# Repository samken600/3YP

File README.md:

# 3YP

## [Project Workspace](project_workspace)

See the [README](project_workspace/README.md) inside for details on setting up RIOT. Note that the RIOT and openocd sub-repositories are managed with git subtrees, NOT submodules. Ensure the correct commands are used when updating these modules.

* Border router files to run on SAMR30 Xplained-Pro boards (`/gnrc_border_router`)

* CoAP server to run on PCBs (`/3yp_node_coap`)

* Testing program to run on PCBs (`/3yp_node_testing`)

* NanoCoAP server to run on SAMR21 boards with DS18 temperature sensor (`/nanocoap_server`)

* Modified RIOT directory (`/RIOT`)

* CoAP server using SAUL, designed to work with different hardware, providing access to LEDs, a temperature sensor and TX power (`/3yp_node_coap_saul`)

* CoAP server and client for automatically PUTting sensor readings and self timestamping packets, designed to work with [coap\_server](coap_server/) and [coap\_forwarder](coap_forwarder) (`3yp_node_coap_saul_puts`)

* Power management testing programs, with and without networking (`periph_pm`, `periph_pm_networking`)

## [PCB Files](pcb/)

* Parts list for PCB
* [Eagle project files](pcb/EAGLE/) (see `/projects/3YP PCB Rev2A` for project and `/libraries` for parts). Can use this as the working directory for EAGLE. 

## [CoAP to HTTP query script](coap-http/)

* Bridge between CoAP and HTTP

* Scheduled script runs every 10 minutes (`coap-http/pipe.py`)

## [Flask Application](flaskApp/)

* Flask webserver files
* HTML and CSS (`/app/static`)
* Temperature HTTP API (`/app/controllers`)
* Graphing webpage/dashboard (`/plotlydash`)

## [Coap Forwarder](coap_forwarder/)

* Using CoAPthon3 with binary token patch
* Acts as forwarder between IPv6 GNRC network and IPv4 outer network
* Only role is to forward packets outside of network

## [Coap Server](coap_server/)

* Using CoAPthon3 with binary token patch
* Provides API to POST temperature data to and GET the current time
* Interfaced with MongoDB in `config.py` and so data served via the flask webserver

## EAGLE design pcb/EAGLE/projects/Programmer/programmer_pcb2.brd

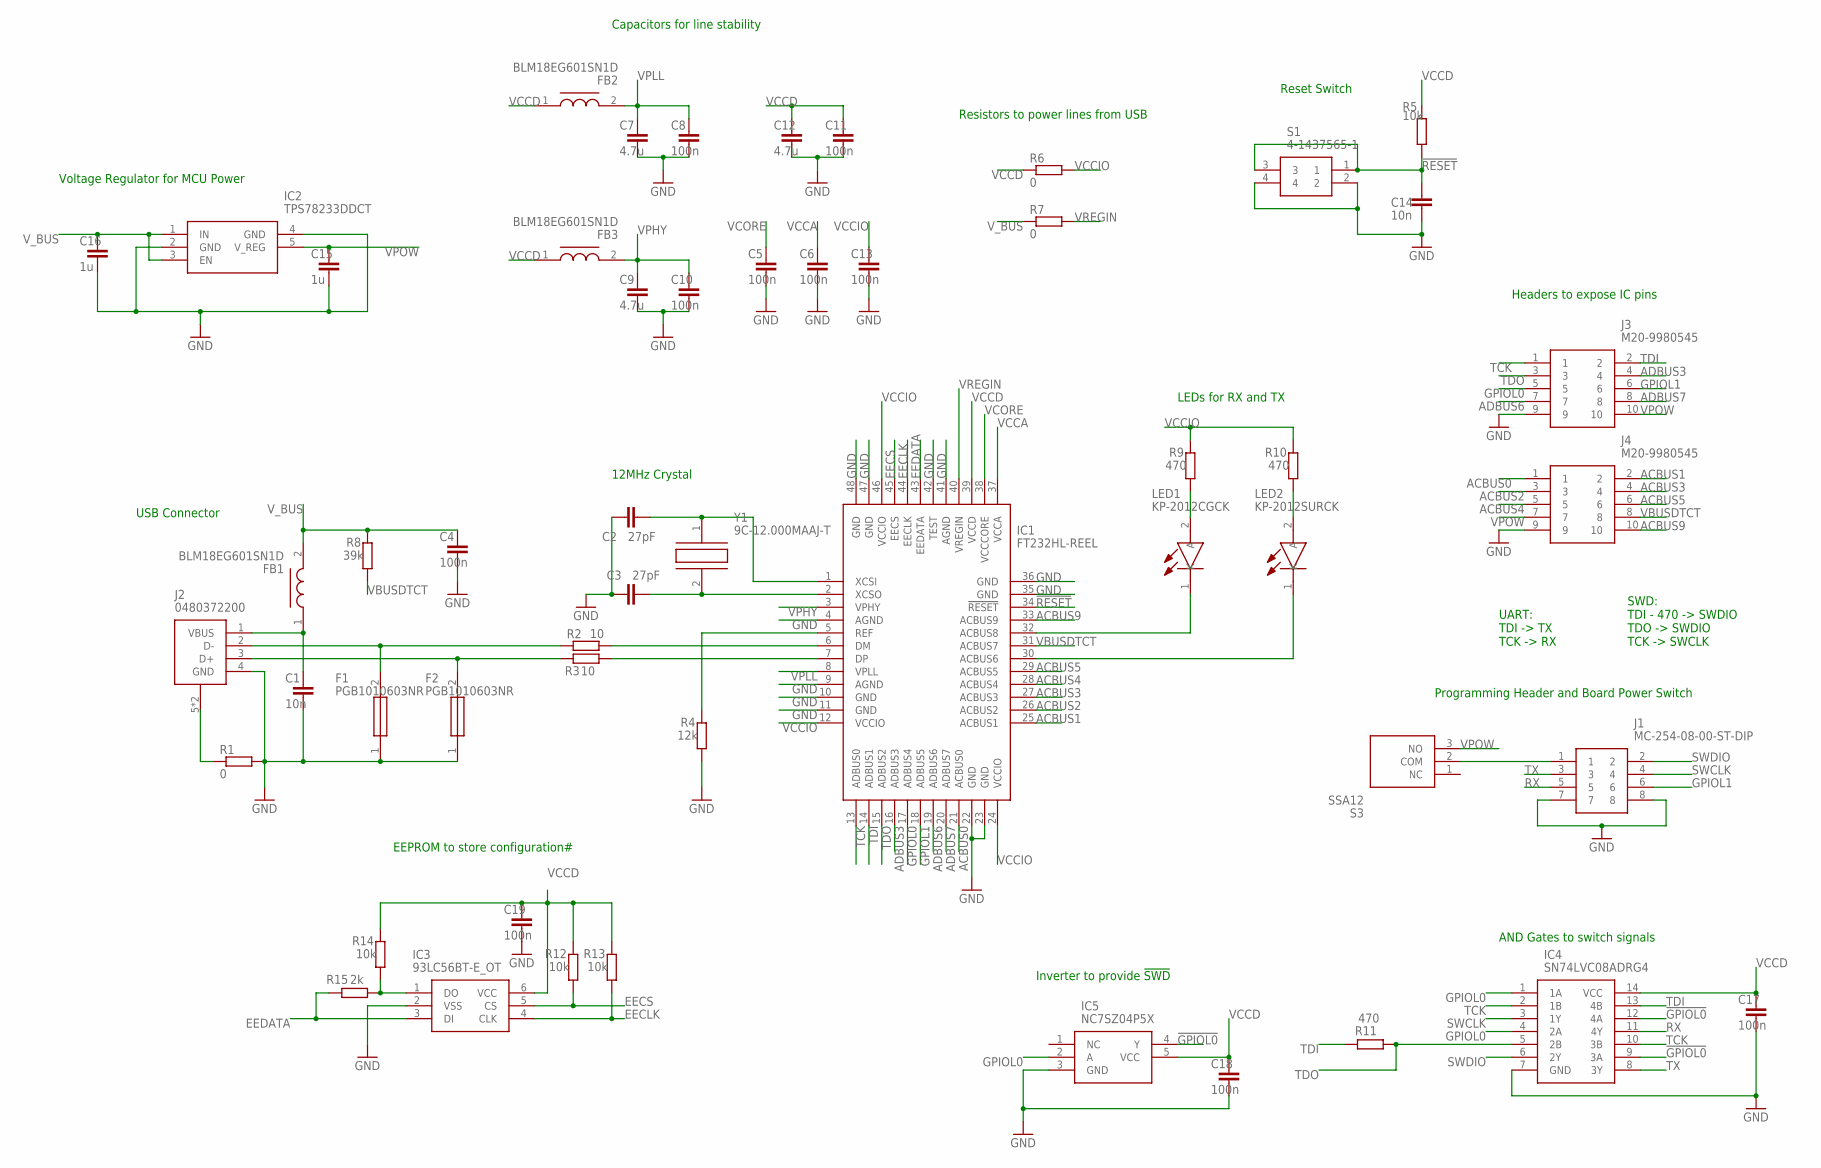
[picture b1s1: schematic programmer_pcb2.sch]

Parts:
C1, C14: 10n; C0805
C2, C3: 27pF; C0805
C4, C5, C6, C8, C10, C11, C13, C17, C18, C19: 100n; C0805
C7, C9, C12: 4.7u; C0805
C15, C16: 1u; C0805
F1, F2: PGB1010603NR; FUSC1708X36N
FB1, FB2, FB3: BLM18EG601SN1D; BLM18EG121SH1D
IC1: FT232HL-REEL; QFP50P900X900X160-48N
IC2: TPS78233DDCT; SOT95P280X110-5N
IC3: 93LC56BT-E_OT; SOT95P270X145-6N
IC4: SN74LVC08ADRG4; SOIC127P600X175-14N
IC5: NC7SZ04P5X; SOT65P210X110-5N
J1: MC-254-08-00-ST-DIP; MC2540800STDIP
J2: 0480372200
J3, J4: M20-9980545; HDRV10W80P254_2X5_1270X508X864
LED1: KP-2012CGCK; LEDC2012X110N
LED2: KP-2012SURCK; LEDC2012X110N
R1, R6, R7: 0; R0603
R2, R3: 10; R0603
R4: 12k; R0603
R5, R12, R13, R14: 10k; R0603
R8: 39k; R0603
R9, R10, R11: 470; R0603
R15: 2k; R0603
S1: 4-1437565-1; FSM-SWITCH
S3: SSA12
Y1: 9C-12.000MAAJ-T; SMD-HC-49-S

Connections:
!GPIOL0: IC4.9 (3A), IC4.12 (4A), IC5.4 (Y)
!RESET: C14.1, IC1.34 (!RESET), R5.1, S1.1, S1.3
ACBUS0: IC1.21 (ACBUS0), J4.1
ACBUS1: IC1.25 (ACBUS1), J4.2
ACBUS2: IC1.26 (ACBUS2), J4.3
ACBUS3: IC1.27 (ACBUS3), J4.4
ACBUS4: IC1.28 (ACBUS4), J4.5
ACBUS5: IC1.29 (ACBUS5), J4.6
ACBUS9: IC1.33 (ACBUS9), J4.10
ADBUS3: IC1.16 (ADBUS3), J3.4
ADBUS6: IC1.19 (ADBUS6), J3.7
ADBUS7: IC1.20 (ADBUS7), J3.8
EECLK: IC1.44 (EECLK), IC3.4 (CLK), R13.1
EECS: IC1.45 (EECS), IC3.5 (CS), R12.1
EEDATA: IC1.43 (EEDATA), IC3.3 (DI), R15.1
GND: C1.2, C2.1, C3.1, C4.2, C5.2, C6.2, C7.2, C8.2, C9.2, C10.2, C11.2, C12.2, C13.2, C14.2, C15.2, C16.2, C17.2, C18.2, C19.2, F1.1, F2.1, IC1.4 (AGND), IC1.9 (AGND), IC1.10 (GND), IC1.11 (GND), IC1.22 (GND), IC1.23 (GND), IC1.35 (GND), IC1.36 (GND), IC1.41 (AGND), IC1.42 (TEST), IC1.47 (GND), IC1.48 (GND), IC2.2 (GND), IC2.4 (GND), IC3.2 (VSS), IC4.7 (GND), IC5.3 (GND), J1.7, J1.8, J2.4 (GND), J3.9, J4.9, R1.2, R4.1, S1.2, S1.4
GPIOL0: IC1.17 (ADBUS4), IC4.1 (1A), IC4.4 (2A), IC5.2 (A), J3.5
GPIOL1: IC1.18 (ADBUS5), J1.6, J3.6
unnamed: J2.5 (SLD), J2.6 (SLD), R1.1
unnamed: C1.1, FB1.1, J2.1 (VBUS)
unnamed: F1.2, J2.2 (D-), R2.1
unnamed: F2.2, J2.3 (D+), R3.1
unnamed: IC1.7 (DP), R3.2
unnamed: IC1.6 (DM), R2.2
unnamed: C2.2, IC1.1 (XCSI), Y1.1
unnamed: C3.2, IC1.2 (XCSO), Y1.2
unnamed: IC1.5 (REF), R4.2
unnamed: J1.1, S3.2 (COM)
unnamed: IC1.30 (ACBUS6), LED2.1 (K)
unnamed: IC1.32 (ACBUS8), LED1.1 (K)
unnamed: LED1.2 (A), R9.1
unnamed: LED2.2 (A), R10.1
unnamed: IC3.1 (DO), R14.1, R15.2
RX: IC4.11 (4Y), J1.5
SWCLK: IC4.3 (1Y), J1.4
SWDIO: IC4.6 (2Y), J1.2
TCK: IC1.13 (ADBUS0), IC4.2 (1B), IC4.10 (3B), J3.1
TDI: IC1.14 (ADBUS1), IC4.13 (4B), J3.2, R11.1
TDO: IC1.15 (ADBUS2), IC4.5 (2B), J3.3, R11.2
TX: IC4.8 (3Y), J1.3
VBUSDTCT: IC1.31 (ACBUS7), J4.8, R8.1
VCCA: C6.1, IC1.37 (VCCA)
VCCD: C11.1, C12.1, C17.1, C18.1, C19.1, FB2.1, FB3.1, IC1.39 (VCCD), IC3.6 (VCC), IC4.14 (VCC), IC5.5 (VCC), R5.2, R6.1, R12.2, R13.2, R14.2
VCCIO: C13.1, IC1.12 (VCCIO), IC1.24 (VCCIO), IC1.46 (VCCIO), R6.2, R9.2, R10.2
VCORE: C5.1, IC1.38 (VCCCORE)
VPHY: C9.1, C10.1, FB3.2, IC1.3 (VPHY)
VPLL: C7.1, C8.1, FB2.2, IC1.8 (VPLL)
VPOW: C15.1, IC2.5 (V_REG), J3.10, J4.7, S3.3 (NO)
VREGIN: IC1.40 (VREGIN), R7.2
V_BUS: C4.1, C16.1, FB1.2, IC2.1 (IN), IC2.3 (EN), R7.1, R8.2

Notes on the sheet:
UART: TDI -> TX TCK -> RX
SWD: TDI - 470 -> SWDIO TDO -> SWDIO TCK -> SWCLK
Voltage Regulator for MCU Power
Capacitors for line stability
Resistors to power lines from USB
Reset Switch
Headers to expose IC pins
LEDs for RX and TX
Programming Header and Board Power Switch
AND Gates to switch signals
Inverter to provide !SWD
EEPROM to store configuration#
USB Connector
12MHz Crystal

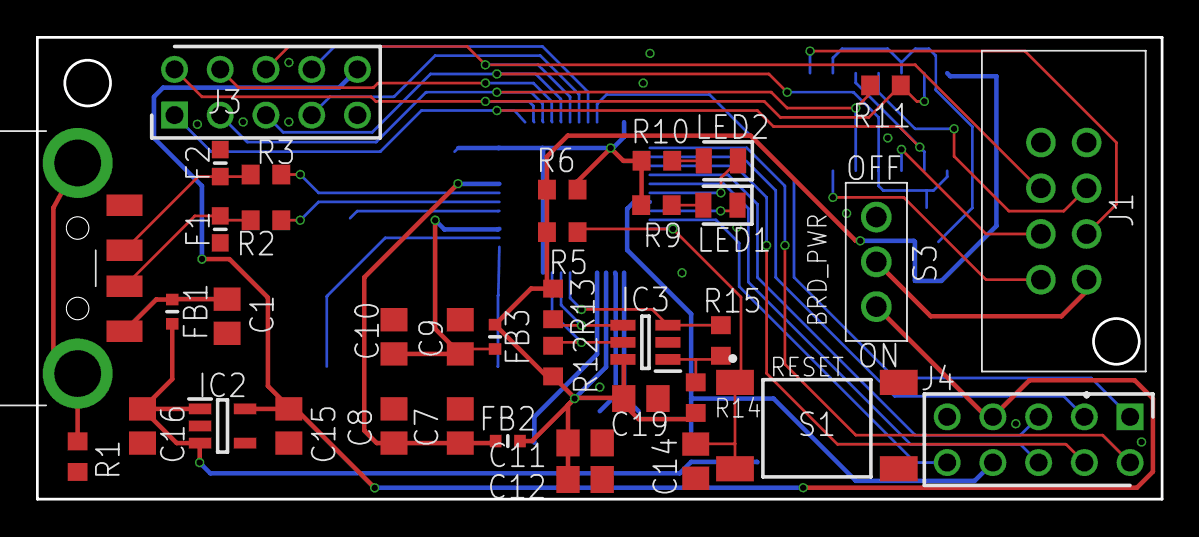
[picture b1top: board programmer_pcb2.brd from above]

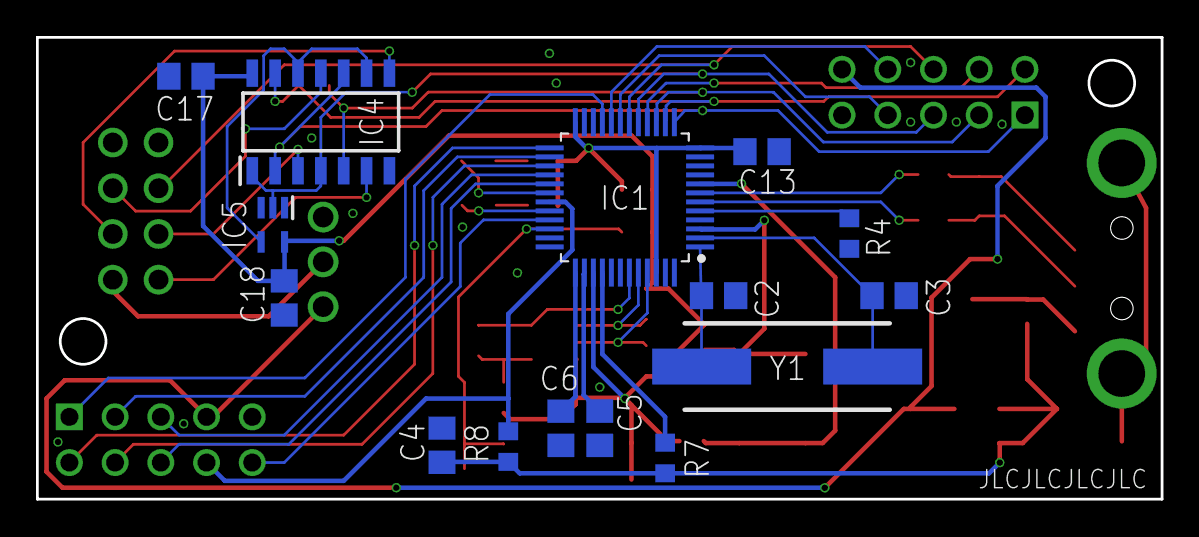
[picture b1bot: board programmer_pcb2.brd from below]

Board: 2 copper layers, 62.5 x 25.7 mm, 53 parts (15 on the bottom side), 50 nets.

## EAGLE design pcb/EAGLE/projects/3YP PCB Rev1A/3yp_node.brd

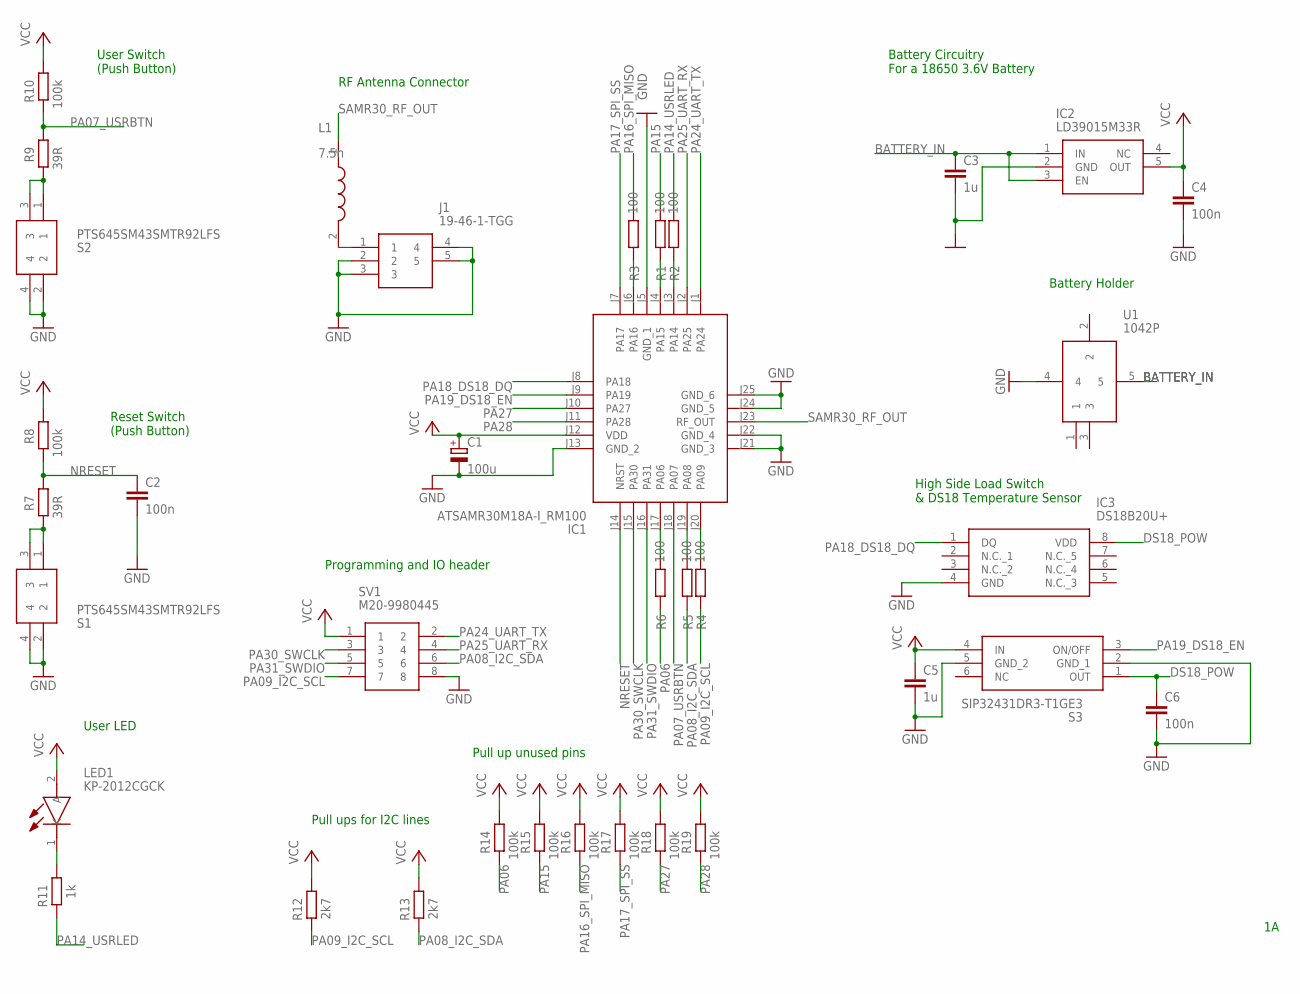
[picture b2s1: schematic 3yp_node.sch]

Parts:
C1: 100u; A/3216-18W
C2, C4, C6: 100n; C0805
C3, C5: 1u; C0805
IC1: ATSAMR30M18A-I_RM100; ATSAMR30M18AIRM100
IC2: LD39015M33R; SOT95P280X145-5N
IC3: DS18B20U+; SOP65P490X110-8N
J1: 19-46-1-TGG; 19-46-1-TGG_1
L1: 7.5n; INDC1006X60N
LED1: KP-2012CGCK; LEDC2012X110N
R1, R2, R3, R4, R5, R6: 100; R0603
R7, R9: 39R; R0603
R8, R10, R14, R15, R16, R17, R18, R19: 100k; R0603
R11: 1k; R0603
R12, R13: 2k7; R0603
S1, S2: PTS645SM43SMTR92LFS; PTS645(SMT)
S3: SIP32431DR3-T1GE3; SOT65P210X110-6N
SV1: M20-9980445; HDRV8W64P254_2X4_1016X508X868P
U1: 1042P

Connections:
BATTERY_IN: C3.1, IC2.1 (IN), IC2.3 (EN), U1.5
DS18_POW: C6.1, IC3.8 (VDD), S3.1 (OUT)
GND: C1.-, C2.2, C3.2, C4.2, C5.2, C6.2, IC1.J5 (GND_1), IC1.J13 (GND_2), IC1.J21 (GND_3), IC1.J22 (GND_4), IC1.J24 (GND_5), IC1.J25 (GND_6), IC2.2 (GND), IC3.4 (GND), J1.2, J1.3, J1.4, J1.5, S1.2, S1.4, S2.2, S2.4, S3.2 (GND_1), S3.5 (GND_2), SV1.8, U1.4
unnamed: R9.2, S2.1, S2.3
unnamed: IC1.J4 (PA15), R1.1
unnamed: IC1.J6 (PA16), R3.1
unnamed: IC1.J3 (PA14), R2.1
unnamed: IC1.J17 (PA06), R6.2
unnamed: IC1.J19 (PA08), R5.2
unnamed: IC1.J20 (PA09), R4.2
unnamed: R7.2, S1.1, S1.3
unnamed: LED1.1 (K), R11.1
unnamed: J1.1, L1.2
NRESET: C2.1, IC1.J14 (NRST), R7.1, R8.2
PA06: R6.1, R14.2
PA07_USRBTN: IC1.J18 (PA07), R9.1, R10.2
PA08_I2C_SDA: R5.1, R13.2, SV1.6
PA09_I2C_SCL: R4.1, R12.2, SV1.7
PA14_USRLED: R2.2, R11.2
PA15: R1.2, R15.2
PA16_SPI_MISO: R3.2, R16.2
PA17_SPI_SS: IC1.J7 (PA17), R17.2
PA18_DS18_DQ: IC1.J8 (PA18), IC3.1 (DQ)
PA19_DS18_EN: IC1.J9 (PA19), S3.3 (ON/OFF)
PA24_UART_TX: IC1.J1 (PA24), SV1.2
PA25_UART_RX: IC1.J2 (PA25), SV1.4
PA27: IC1.J10 (PA27), R18.2
PA28: IC1.J11 (PA28), R19.2
PA30_SWCLK: IC1.J15 (PA30), SV1.3
PA31_SWDIO: IC1.J16 (PA31), SV1.5
SAMR30_RF_OUT: IC1.J23 (RF_OUT), L1.1
VCC: C1.+, C4.1, C5.1, IC1.J12 (VDD), IC2.5 (OUT), LED1.2 (A), R8.1, R10.1, R12.1, R13.1, R14.1, R15.1, R16.1, R17.1, R18.1, R19.1, S3.4 (IN), SV1.1

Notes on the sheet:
Reset Switch (Push Button)
User Switch (Push Button)
Pull ups for I2C lines
High Side Load Switch & DS18 Temperature Sensor
Programming and IO header
Battery Circuitry For a 18650 3.6V Battery
User LED
RF Antenna Connector
Battery Holder
Pull up unused pins

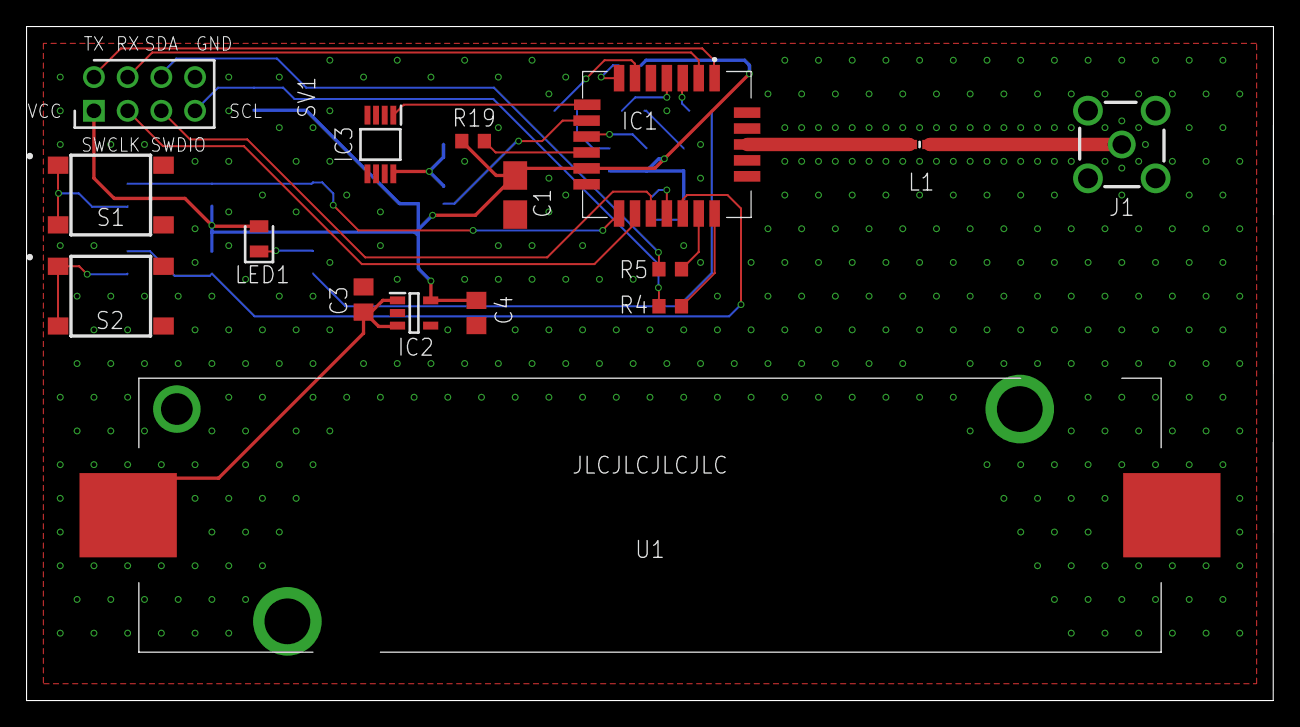
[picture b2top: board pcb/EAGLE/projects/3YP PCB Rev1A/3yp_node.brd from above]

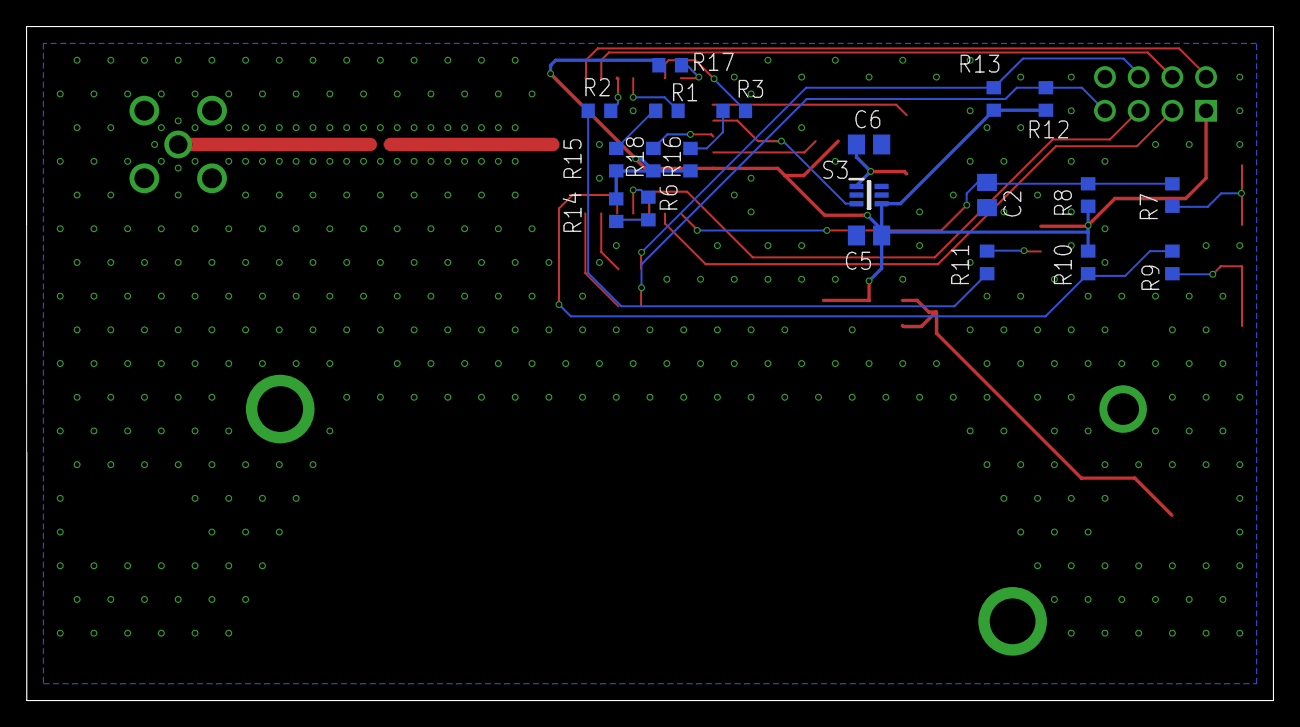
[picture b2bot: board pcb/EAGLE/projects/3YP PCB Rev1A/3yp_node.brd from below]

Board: 2 copper layers, 94.0 x 50.8 mm, 36 parts (20 on the bottom side), 32 nets.

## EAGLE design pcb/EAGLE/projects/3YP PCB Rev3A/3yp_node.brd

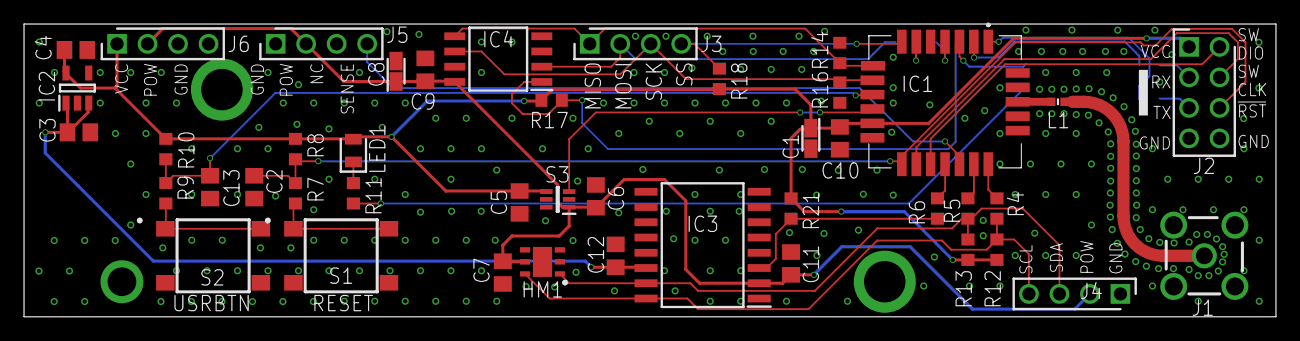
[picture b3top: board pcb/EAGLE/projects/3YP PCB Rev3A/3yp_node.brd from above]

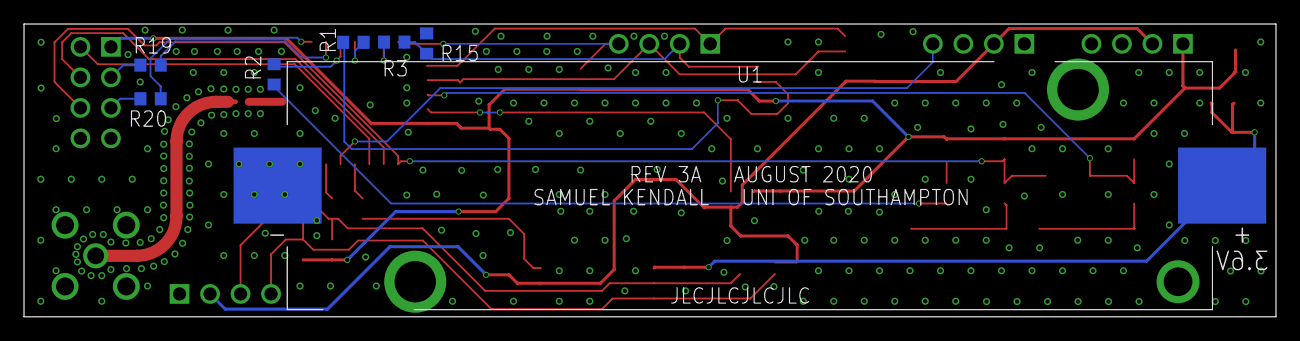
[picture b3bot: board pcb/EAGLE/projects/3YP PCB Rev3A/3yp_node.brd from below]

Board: 2 copper layers, 104.3 x 24.4 mm, 51 parts (7 on the bottom side), 34 nets.

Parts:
C1, C8: 10u; CAPPM2014X170N
C2, C6, C7, C9, C10, C11, C12, C13: 100n; C0805
C3, C4, C5: 1u; C0805
HM1: HDC1080DMBT; SON100P300X300X80-7N
IC1: ATSAMR30M18A-I_RM100; ATSAMR30M18AIRM100
IC2: TPS78233DDCT; SOT95P280X110-5N
IC3: DS3231SN#; SOIC127P1032X265-16N
IC4: AT25DF321A-SH-B; SOIC127P798X216-8N
J1: 19-46-1-TGG; 19-46-1-TGG_1
J2: M20-9980445; HDRV8W64P254_2X4_1016X508X868P
J3, J4, J5, J6: M20-9990445; HDRV4W64P0X254_1X4_1016X254X86
L1: 7.5n; INDC1006X60N
LED1: KP-2012CGCK; LEDC2012X110N
R1, R2, R3, R4, R5, R6: 100; R0603
R7, R9: 39R; R0603
R8, R10, R14, R15, R16, R17, R18, R21: 100k; R0603
R11, R19, R20: 1k; R0603
R12, R13: 2k7; R0603
S1, S2: PTS645SM43SMTR92LFS; PTS645(SMT)
S3: SIP32431DR3-T1GE3; SOT65P210X110-6N
U1: 1042P

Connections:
!PA15_SPI_FLASH_SS: IC4.1, R1.2, R17.2
BATTERY_IN: C3.1, C12.1, IC2.1, IC2.3, IC3.14, U1.5
GND: C1.2, C2.2, C3.2, C4.2, C5.2, C6.2, C7.2, C8.2, C9.2, C10.1, C11.2, C12.2, C13.2, HM1.2, HM1.3, HM1.4, IC1.J5, IC1.J13, IC1.J21, IC1.J22, IC1.J24, IC1.J25, IC2.2, IC2.4, IC3.5, IC3.6, IC3.7, IC3.8, IC3.9, IC3.10, IC3.11, IC3.12, IC3.13, IC4.4, J1.2, J1.3, J1.4, J1.5, J2.7, J2.8, J4.1, J5.1, J6.3, J6.4, R14.2, R15.2, R16.2, S1.3, S1.4, S2.3, S2.4, S3.2, S3.5, U1.4
unnamed: R9.2, S2.1, S2.2
unnamed: IC1.J4, R1.1
unnamed: IC1.J6, R3.1
unnamed: IC1.J3, R2.1
unnamed: IC1.J17, R6.2
unnamed: IC1.J19, R5.2
unnamed: IC1.J20, R4.2
unnamed: R7.2, S1.1, S1.2
unnamed: LED1.1, R11.1
unnamed: J1.1, L1.2
unnamed: IC1.J2, R19.1
unnamed: IC1.J1, R20.1
NRESET: C2.1, IC1.J14, J2.6, R7.1, R8.2
PA06_RTC_INT: IC3.3, R6.1, R21.2
PA07_ANALOG: IC1.J18, J5.4
PA08_I2C_SDA: HM1.1, IC3.15, J4.3, R5.1, R13.2
PA09_I2C_SCL: HM1.6, IC3.16, J4.4, R4.1, R12.2
PA14_USRLED: R2.2, R11.2
PA16_SPI_MISO: IC4.2, J3.2, R3.2, R15.1
PA17_SPI_SS: IC1.J7, J3.4, R18.2
PA18_SPI_MOSI: IC1.J8, IC4.5, J3.1, R14.1
PA19_SPI_SCK: IC1.J9, IC4.6, J3.3, R16.1
PA24_UART_TX: J2.5, R20.2
PA25_UART_RX: J2.3, R19.2
PA27_USRBTN: C13.1, IC1.J10, R9.1, R10.2
PA28_SENSOR_POW: IC1.J11, S3.3
PA30_SWCLK: IC1.J15, J2.4
PA31_SWDIO: IC1.J16, J2.2
SAMR30_RF_OUT: IC1.J23, L1.1
SENSOR_POW: C6.1, C7.1, C8.1, C9.1, C11.1, HM1.5, IC3.2, IC4.8, J4.2, J5.2, J6.2, S3.1
VCC: C1.1, C4.1, C5.1, C10.2, IC1.J12, IC2.5, J2.1, J6.1, LED1.2, R8.1, R10.1, R12.1, R13.1, R17.1, R18.1, R21.1, S3.4

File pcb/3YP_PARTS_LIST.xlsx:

NAME ON BOARD | PART | DESCRIPTION | NO. REQUIRED (PER BOARD) | SUPPLIER | ORDER NUMBER | MANUF. PART NUM. | URL | Cost/unit | Min Order | Number Required N Boards | Order required | Cost | With VAT
U1 | 1 | 18650 Battery Holder SMT Polarised | 1 | MOUSER | 534-1042P | 1042P | https://www.mouser.co.uk/ProductDetail/Keystone-Electronics/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 | 1.87 | 1 | 5 | 4 | 7.48 | 8.9760000000000009
S1, S2 | 2 | SMT Tactile Switch | 2 | ONECALL | 2320087 | PTS645SM43SMTR92LFS | https://onecall.farnell.com/c-k-components/pts645sm43smtr92l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 | 0.192 | 10 | 10 | 10 | 1.92 | 2.3039999999999998
LED1 | 3 | Low Power Green SMD LED | 1 | ONECALL | 2290331 | KP-2012CGCK | https://onecall.farnell.com/kingbright/kp-2012cgck/led-0805-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 | 0.126 | 5 | 5 | 5 | 0.63 | 0.75600000000000001
IC1 | 4 | Castellated SAMR30 SoC | 1 | ONECALL | 3013705 | ATSAMR30M18A-I/RM100 | https://onecall.farnell.com/microchip/atsamr30m18a-i-rm100/m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 | 4.93 | 1 | 5 | 5 | 24.65 | 29.58
- | 5 | 3.6V 18650 Li-ion 2Ah Battery | 1 | RS | 818-2992 | INR-18650 20R | https://uk.rs-online.com/web/p/speciality-size-rechargeable-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 | 5.67 | 1 | 5 | 5 | 28.35 | 34.020000000000003
IC3 | 6 | 1-Wire Temperature Sensor | 1 | ONECALL | 2518694 | DS18B20U+ | https://onecall.farnell.com/maxim-integrated-products/ds18b2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 | 2.4900000000000002 | 1 | 5 | 0 | 0 | 0
J1 | 7 | RF Coaxial Connector SMA 50ohm | 1 | ONECALL | 1169631 | 19-46-1-TGG | https://onecall.farnell.com/multicomp/19-46-1-tgg/rf-coaxial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 | 3.53 | 1 | 5 | 5 | 17.649999999999999 | 21.179999999999996
C1, C8 | 8 | 10uF Tantalum Capacitor 6.3V SMD 0805 | 2 | ONECALL | 1658203 | TAJP106K006RNJ | https://onecall.farnell.com/avx/tajp106k006rnj/cap-10-f-6-3v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 | 0.57999999999999996 | 5 | 10 | 10 | 5.8 | 6.96
C2, C6, C7, C9, C10 | 9 | 100nF SMD Multilayer Ceramic Capacitor 0805 | 5 | ONECALL | 2332715 | 08051C104JAT2A | https://onecall.farnell.com/avx/08051c104jat2a/cap-0-1-f-100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 | 0.23400000000000001 | 5 | 25 | 25 | 5.8500000000000005 | 7.0200000000000005
L1 | 10 | 7.5nH Multilayer Inductor 0402 | 1 | ONECALL | 1669587 | MLG1005S7N5J | https://onecall.farnell.com/tdk/mlg1005s7n5j/inductor-7-5nh-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 | 4.7100000000000003E-2 | 10 | 5 | 10 | 0.47100000000000003 | 0.56520000000000004
R8, R10 | 11 | 100k SMD Resistor 0603 | 2 | ONECALL | 1577632 | ERA3AEB104V | https://onecall.farnell.com/panasonic/era3aeb104v/res-100k-0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 | 0.28100000000000003 | 10 | 10 | 10 | 2.8100000000000005 | 3.3720000000000003
R1, R2, R3, R4, R5, R6 | 12 | 100R SMD Resistor 0603 | 6 | ONECALL | 9238360 | RC0603FR-07100RL | https://onecall.farnell.com/yageo/rc0603fr-07100rl/res-100r-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 | 0.02 | 10 | 30 | 30 | 0.6 | 0.72
R7, R9 | 13 | 39R SMD Resistor 0603 | 2 | ONECALL | 9238310 | RC0603FR-0739RL | https://onecall.farnell.com/yageo/rc0603fr-0739rl/res-39r-1-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 | 2.06E-2 | 10 | 10 | 10 | 0.20600000000000002 | 0.2472
R11 | 14 | 1k SMD Resistor 0603 | 1 | ONECALL | 9238484 | RC0603FR-071KL | https://onecall.farnell.com/yageo/rc0603fr-071kl/res-1k-1-0-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 | 0.02 | 10 | 5 | 10 | 0.2 | 0.24
R12, R13 | 15 | 2k7 SMD Resistor 0603 | 2 | ONECALL | 9238530 | RC0603FR-072K7L | https://onecall.farnell.com/yageo/rc0603fr-072k7l/res-2k7-1-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 | 0.02 | 10 | 10 | 10 | 0.2 | 0.24
SV1 | 16 | 2.54mm Pin Header 2 Rows THT | 1 | ONECALL | 1022232 | M20-9980445 | https://onecall.farnell.com/harwin/m20-9980445/connector-hea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 | 0.26 | 10 | 5 | 10 | 2.6 | 3.12
S3 | 17 | High Side Power Load Switch 5.5V 1A | 1 | RS | 180-7822 | SIP32431DR3-T1GE3 | https://uk.rs-online.com/web/p/mosfets/1807822/ | 0.35 | 25 | 5 | 25 | 8.75 | 10.5
IC2 | 18 | Linear Voltage Regulator 3.3V 0.15A | 1 | ONECALL | 2311333 | LD39015M33R | https://onecall.farnell.com/stmicroelectronics/ld39015m33r/v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 | 0.68600000000000005 | 1 | 5 | 5 | 3.43 | 4.1159999999999997
C3, C4, C5 | 19 | 1uF SMD Multilayer Ceramic Capacitor 0805 | 3 | ONECALL | 2346940 | C2012X7R1E105K125AB | https://onecall.farnell.com/tdk/c2012x7r1e105k125ab/cap-1-f-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 | 0.185 | 5 | 15 | 15 | 2.7749999999999999 | 3.3299999999999996
J2 | 20 | 2.54mm Pin Header 4 Contact 1 Row THT | 1 | ONECALL | 2856691 | TSW-104-07-F-S | https://onecall.farnell.com/samtec/tsw-104-07-f-s/connector-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 | 0.23 | 10 | 5 | 10 | 2.3000000000000003 | 2.7600000000000002
IC4 | 21 | 32Mbit SPI Flash WSOIC-8 | 1 | ONECALL | 2909992 | AT25DF321A-SH-T | https://onecall.farnell.com/adesto-technologies/at25df321a-s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 | 2.1800000000000002 | 1 | 5 | 0 | 0 | 0
HW1 | 22 | Low Power Temp/Humidity Sensor I2C 3V3 | 1 | ONECALL | 3105971 | SI7006-A20-IM1R | https://onecall.farnell.com/silicon-labs/si7006-a20-im1r/hum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 | 2.44 | 1 | 5 | 5 | 12.2 | 14.639999999999999
- | 23 | SMA 868MHz Whip Antenna 50ohm | 1 | RS | 532-4430 | ANT-900MS | https://uk.rs-online.com/web/p/telemetry-antennas/5324430/ | 3.56 | 1 | 5 | 5 | 17.8 | 21.36
 |  |  |  |  |  |  |  |  |  |  |  | Total: | 176.00639999999993
 |  |  |  |  |  |  |  |  |  |  |  | Per board: | 35.201279999999983
 |  |  |  |  |  |  |  | N Boards | 5
 |  | https://api.element14.com/catalog/products?versionNumber=1.1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 |  | http://octopart.com/api/v3/parts/match?apikey=92bdca1b&queri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 '232083… |  | https://octopart.com/api/docs/v3/overview

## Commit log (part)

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2020-01-31 Initial commit. Bit late into project
2020-01-31 Oops, removing dir
2020-01-31 Updated gitignore
2020-01-31 rename
2020-01-31 Squashed 'openocd2/' content from commit 09ac9ab1
    git-subtree-dir: openocd2
    git-subtree-split: 09ac9ab135ed35c846bcec4f7d468c3656852f26
2020-01-31 Removed fake
2020-01-31 Squashed 'openocd/' content from commit 09ac9ab1
    git-subtree-dir: openocd
    git-subtree-split: 09ac9ab135ed35c846bcec4f7d468c3656852f26
2020-01-31 Adding config files for swd over c232hm cable and mz210pa module
2020-01-31 Rename riot and remove old openocd
2020-01-31 Squashed 'project_workspace/RIOT/' content from commit 1506ed3d22
    git-subtree-dir: project_workspace/RIOT
    git-subtree-split: 1506ed3d22c50261cfad16de2b005b460468dd5d
2020-01-31 Moved over to tree properly
2020-02-02 Trying to fix openocd
2020-02-02 Update url
2020-02-02 Updating
2020-02-03 Removed submodule
2020-02-03 Removed submodules
2020-02-03 Readded submodules
2020-02-06 Fully working RPL and temp. sensors power off via pin toggle
2020-02-06 This makes no sense
2020-02-06 Squashed 'project_workspace/RIOT/' changes from 1506ed3d22..8735f8176a
    8735f8176a Merge pull request #13274 from fjmolinas/pr_2020.01-branch-VERSION
    5aafd52359 VERSION: add 2020.01 version file
    5a75d991d5 Merge pull request #13272 from fjmolinas/backport/2020.01/2020.01-release-notes
    98a1a2dd17 release-notes.txt: add 2020.01 release notes
    97f8832003 Merge pull request #13237 from MichelRottleuthner/pr_bp13212
    a310ff9c98 sys/xtimer: compare two offsets rather than absolute times
2020-02-07 Got ecn28j60 working. Just do make flash term
2020-02-07 Removed old file
2020-02-12 Added in some extra printout
2020-02-12 Starting gomach work
2020-02-12 Removed old lib
2020-02-12 RPL default NETIF configured for GoMACH
2020-02-12 Ignoring temp/
2020-02-12 Updated drive a little to deal with receives a little better. Reliability seems to be improved
2020-02-14 Added gitignore and debug line
2020-02-14 Match
2020-02-18 Moved to lwmac
2020-02-18 Tweaking settings to work with SAMR30
2020-02-18 Adapting for SAMR30
2020-03-04 Adding PCB stuff
2020-03-04 Moved and merged
2020-03-05 Added parts list and amlost finished with schematic
2020-03-06 New board version!
2020-03-07 Updated board
2020-03-08 Not too sure what has changed, but am sure something has
2020-03-09 Finalising board...
2020-03-09 Fixed parts list
2020-03-09 Fixed overlap
2020-03-10 Updated parts list
2020-03-10 Regenned files
2020-03-11 Added antenna
2020-03-11 Ordering parts. Crossed some off
2020-03-11 Added ham hw to gitignore
2020-03-14 Corrected pins
2020-03-14 Added in LWMAC. Not working though
2020-03-14 Working on LWMAC
2020-03-14 Squashed 'project_workspace/RIOT/' changes from 8735f8176a..d281d4843f
    d281d4843f Merge pull request #13628 from jia200x/pr/gnrc_rpl_macro
    c974451591 Merge pull request #11315 from fjmolinas/pr_im880b
    55b11b7925 boards/im880b: add insufficient memory to tests
    e4a3c29fca boards/im880b: enable paboost on sx127x
    4618a5ce0e boards/im880b: add initial support
    b553535cea gnrc_rpl_auto_init: replace preprocessor logic with if chain
2020-03-15 Changed page, seems to fix issues
2020-03-15 Disabled debug mode
2020-03-15 Adjusting clock freq
2020-03-20 Adding in low power mode and configuring timings. Working for short periods (untested how long), seems to break down after a while
2020-03-20 Increase mac queue sizes for better reliability
2020-03-27 Updated ignore
2020-05-05 Id seems to not be working, hardcoded
2020-05-05 Adding support for 3yp node
2020-05-05 Adding report stuff i.e. gantt chart and risk
2020-05-05 Notes on stuff
2020-05-05 Added 3yp node stuff but without lwmac
2020-05-12 Testing power
2020-05-12 Readded power test
2020-05-12 Re-enabled LWMAC
2020-05-12 Reverted to warnings and above for lwmac
2020-05-12 Added 3YP-node code with CoAP
2020-05-12 Minor changes to gantt chart and formatting changes to parts list
2020-05-13 Added flask server
2020-05-13 Removed flaskEnv files
2020-05-18 minor change
2020-05-18 Added graph refresh button. Need to format
2020-05-18 Moved button
2020-05-18 Increasing timings...
2020-05-18 Removed old packages
2020-05-18 Added coap-http script
2020-05-18 Cleaning up
2020-05-19 Reverted buffer size to default
2020-05-19 Reverted buffer size
2020-05-19 Fixed break if one node doesn't respond
2020-05-19 Changed timings and commented originals
2020-05-19 Updated timings
2020-06-02 Added headers for documentation
2020-07-07 Added program for testing power
2020-07-07 Cleaning up and moving stuff
2020-07-07 Adding in off power mode
2020-07-07 Tweaking timing
2020-07-07 Adding in at86rf2xx drivers to turn off radio
2020-07-07 Squashed 'project_workspace/RIOT/' changes from d281d4843f..db5070c772
    db5070c772 Merge pull request #14441 from miri64/riotctrl_shell/feat/netif
    fe7700c7de Merge pull request #14444 from akshaim/Kconfig_asymcute
    637b1df9d4 Merge pull request #14446 from leandrolanzieri/pr/drivers/atca_doc_group_config
    7a2e9c8948 net/asymcute : Update documentation
    e9f270c78a net/asymcute : Expose to Kconfig
    8a6d2882f7 net/asymcute : Move 'ASYMCUTE_KEEPALIVE_PING' to 'CONFIG_'
2020-07-07 Cleaning up for new riot version
2020-07-07 Rolling back timing changes
2020-07-07 Changed clock source
2020-07-16 Finishing up power testing
2020-07-23 Sensor power added to board initialisation
2020-07-23 Removed LWMAC from border router for testing
2020-07-23 Added CoAP SAUL example
2020-07-27 Auto init rpl
2020-07-27 Cleaning up old code and added CoAP put/get functionality
2020-07-27 Adding folders to run CoAP server and forwarder. Server will run in parallel on VPS and store in db, forwarder will do ipv6 -> ipv4 on laptop
2020-07-27 Fixing venv stuff for coap services
2020-07-27 Added pymongo config
2020-07-27 setting up files
2020-07-28 Fixing version issue
2020-07-28 Roll back changes to si70xx
2020-07-29 Improving CoAP server structure and adding resources
2020-07-29 Bump urllib3 from 1.21.1 to 1.24.2 in /flaskApp
    Bumps [urllib3](https://github.com/urllib3/urllib3) from 1.21.1 to 1.24.2.
    - [Release notes](https://github.com/urllib3/urllib3/releases)
    - [Changelog](https://github.com/urllib3/urllib3/blob/master/CHANGES.rst)
    - [Commits](https://github.com/urllib3/urllib3/compare/1.21.1...1.24.2)
2020-07-29 CoAP Proxy Setup
2020-07-29 Bump requests from 2.18.1 to 2.20.0 in /flaskApp
    Bumps [requests](https://github.com/psf/requests) from 2.18.1 to 2.20.0.
    - [Release notes](https://github.com/psf/requests/releases)
    - [Changelog](https://github.com/psf/requests/blob/master/HISTORY.md)
    - [Commits](https://github.com/psf/requests/compare/v2.18.1...v2.20.0)
2020-07-29 Added in delay for sensor reading. 250ms
2020-07-29 Removed CoAP client code so only acts as server, simplify
2020-07-29 CoAP client working with server
2020-07-29 Added pymongo to requirements
2020-07-29 Added cachetools to requirements
2020-07-29 Updated Flask, Plotly and requests
2020-07-29 Changed some string formatting
2020-07-29 Added in new API for revised database format
2020-07-29 Updated to fit new API
2020-07-29 Updating to new api
2020-07-30 Refactored code
2020-07-30 Added automatic gets
2020-07-30 Removed unneeded functions
2020-07-31 updated rtc to use internal rather than internal ultra low power
2020-07-31 Program now works! Need to add in sleeping and handle when messages fail to send
2020-08-01 Squashed 'coapthon3/' content from commit 89d51737a9
    git-subtree-dir: coapthon3
    git-subtree-split: 89d51737a9f95a0dbd113a27f4ba88fe6230859f
2020-08-02 Switching to using local coapthon3
2020-08-02 Squashed 'coapthon3/' changes from 89d51737a9..b13f8a5496
    b13f8a5496 [B] send_ack in transaction lock and only if type nad message id are valid
    5bebe167a9 Cleanup - removed obsolete imports - Location-Path and Location-Query only in answers with "Created" Status - Fixed / for root-resource as RemoteResource for reverse-proxy - Fixed parsing 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
    2eafa64308 Token stored as bytes and not limited to ascii chars anymore
    36fb9f243a Respect binary coded payload data
    3c7b11c149 Clean up logger-calls - more semetrical through out the code
    b77fc78dde Speed up unittests, only wait 1 second instead of 10 second
2020-08-02 Moving coap-http to local coapthon3
2020-08-02 Moving coap_server to local coapthon3
2020-08-02 Changing logger level to info
2020-08-03 Updated stuff and fixed bugs, added in queue
2020-08-03 Fixed queue to not loop 8 times
2020-08-03 cleaning up debug
2020-08-05 Removed unneeded code
2020-08-05 Squashed 'project_workspace/RIOT/' changes from db5070c7727..75ec114f819
    75ec114f819 Merge pull request #14693 from fjmolinas/backport/2020.07/fix_msp430_thread_yield_higher
    34c360fa7c8 cpu/msp430_common: fix thread_yield_higher() when called in isr
    f4580e8d847 Merge pull request #14686 from miri64/backport/2020.07/gnrc_sixlowpan_frag_vrb/fix/cppcheck-warning
    d4619d24ee9 gnrc_sixlowpan_frag_vrb: fix cppcheck warning
    2d0180a090f Merge pull request #14671 from maribu/backport/2020.07/pkg_lwip
    957518f9b29 pkg/lwip: Use IS_ACTIVE() & NETCONNTYPE_ISIPV6()
2020-08-06 Reverting riot mods
2020-08-06 Adding in comments
2020-08-07 Added README
2020-08-07 Cleaned up hardware specific code
2020-08-07 Updating README files
2020-08-07 Adding forgotten comments
2020-08-07 Updating READMEs and gitignore
2020-08-07 update README. fix for LIBUSB_ERROR_ACCESS
2020-08-08 Fixing static problem and removing prints
2020-08-10 Fixed unused variable
2020-08-12 New board revision 3A
2020-08-14 Updating swd
2020-08-20 fixing rpl define
2020-08-20 Misc changes
2020-08-20 Finished node layout and added programmer PCB
2020-09-03 Adjusted parameters
2020-10-30 Updating for new board
2020-10-30 Added new headers
2020-10-30 Assorted updates...
2020-10-30 Schematic image
2021-03-20 Bump jinja2 from 2.11.2 to 2.11.3 in /flaskApp
    Bumps [jinja2](https://github.com/pallets/jinja) from 2.11.2 to 2.11.3.
    - [Release notes](https://github.com/pallets/jinja/releases)
    - [Changelog](https://github.com/pallets/jinja/blob/master/CHANGES.rst)
    - [Commits](https://github.com/pallets/jinja/compare/2.11.2...2.11.3)
2021-06-02 Bump urllib3 from 1.25.9 to 1.26.5 in /coap-http
    Bumps [urllib3](https://github.com/urllib3/urllib3) from 1.25.9 to 1.26.5.
    - [Release notes](https://github.com/urllib3/urllib3/releases)
    - [Changelog](https://github.com/urllib3/urllib3/blob/main/CHANGES.rst)
    - [Commits](https://github.com/urllib3/urllib3/compare/1.25.9...1.26.5)
    ---
    updated-dependencies:
2021-06-02 Bump urllib3 from 1.25.10 to 1.26.5 in /flaskApp
    Bumps [urllib3](https://github.com/urllib3/urllib3) from 1.25.10 to 1.26.5.
    - [Release notes](https://github.com/urllib3/urllib3/releases)
    - [Changelog](https://github.com/urllib3/urllib3/blob/main/CHANGES.rst)
    - [Commits](https://github.com/urllib3/urllib3/compare/1.25.10...1.26.5)
    ---
    updated-dependencies:
2022-06-22 Bump numpy from 1.18.4 to 1.22.0 in /flaskApp
    Bumps [numpy](https://github.com/numpy/numpy) from 1.18.4 to 1.22.0.
    - [Release notes](https://github.com/numpy/numpy/releases)
    - [Changelog](https://github.com/numpy/numpy/blob/main/doc/HOWTO_RELEASE.rst)
    - [Commits](https://github.com/numpy/numpy/compare/v1.18.4...v1.22.0)
    ---
    updated-dependencies:
2022-12-08 Bump certifi from 2020.4.5.1 to 2022.12.7 in /coap-http
    Bumps [certifi](https://github.com/certifi/python-certifi) from 2020.4.5.1 to 2022.12.7.
    - [Release notes](https://github.com/certifi/python-certifi/releases)
    - [Commits](https://github.com/certifi/python-certifi/compare/2020.04.05.1...2022.12.07)
    ---
    updated-dependencies:
    - dependency-name: certifi
